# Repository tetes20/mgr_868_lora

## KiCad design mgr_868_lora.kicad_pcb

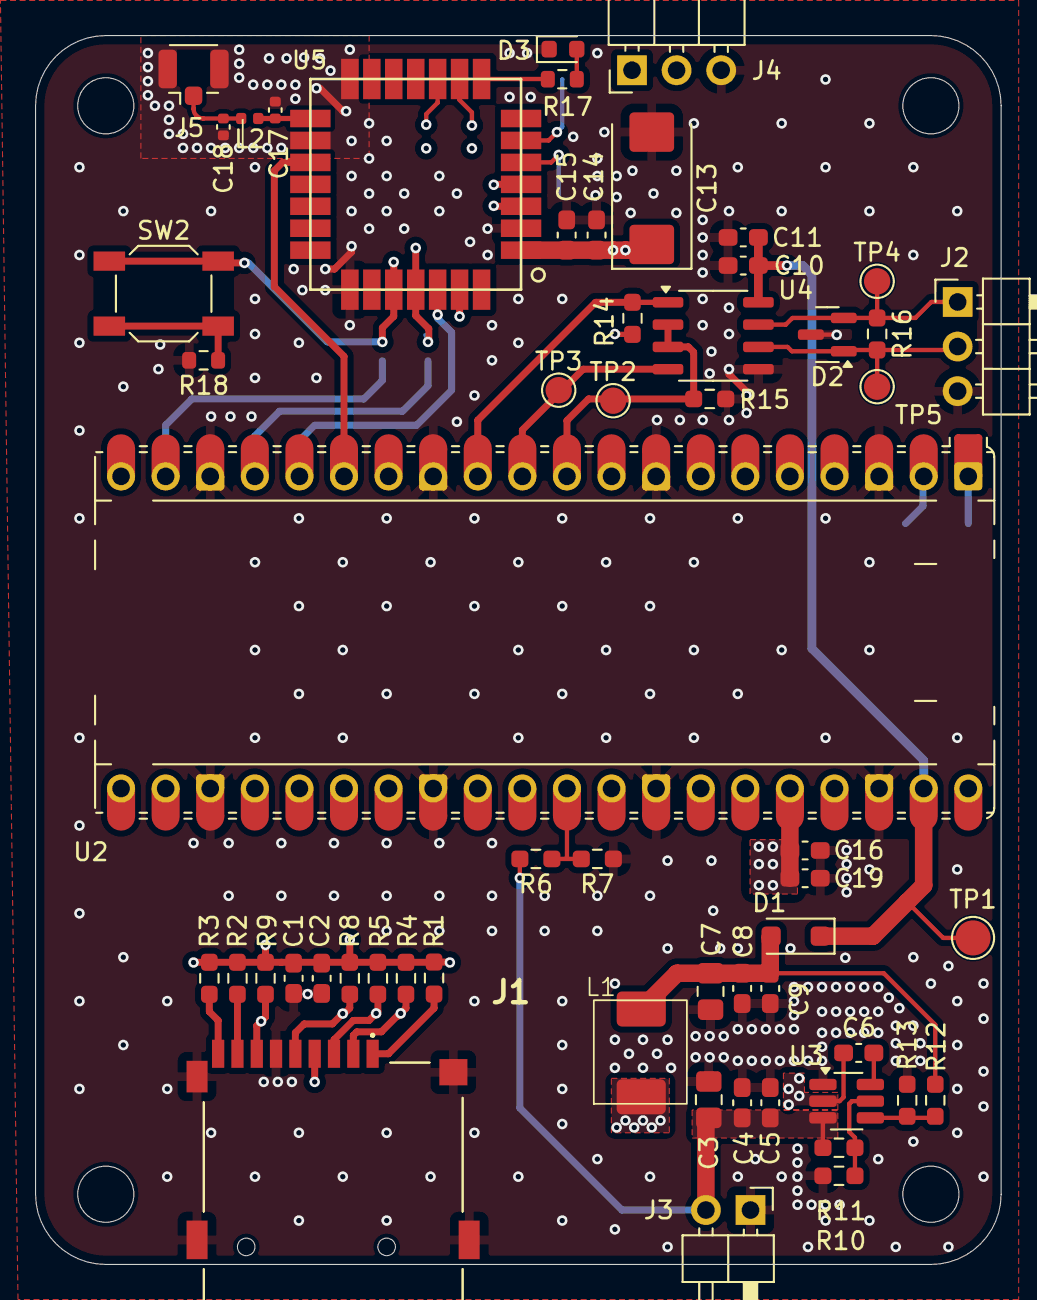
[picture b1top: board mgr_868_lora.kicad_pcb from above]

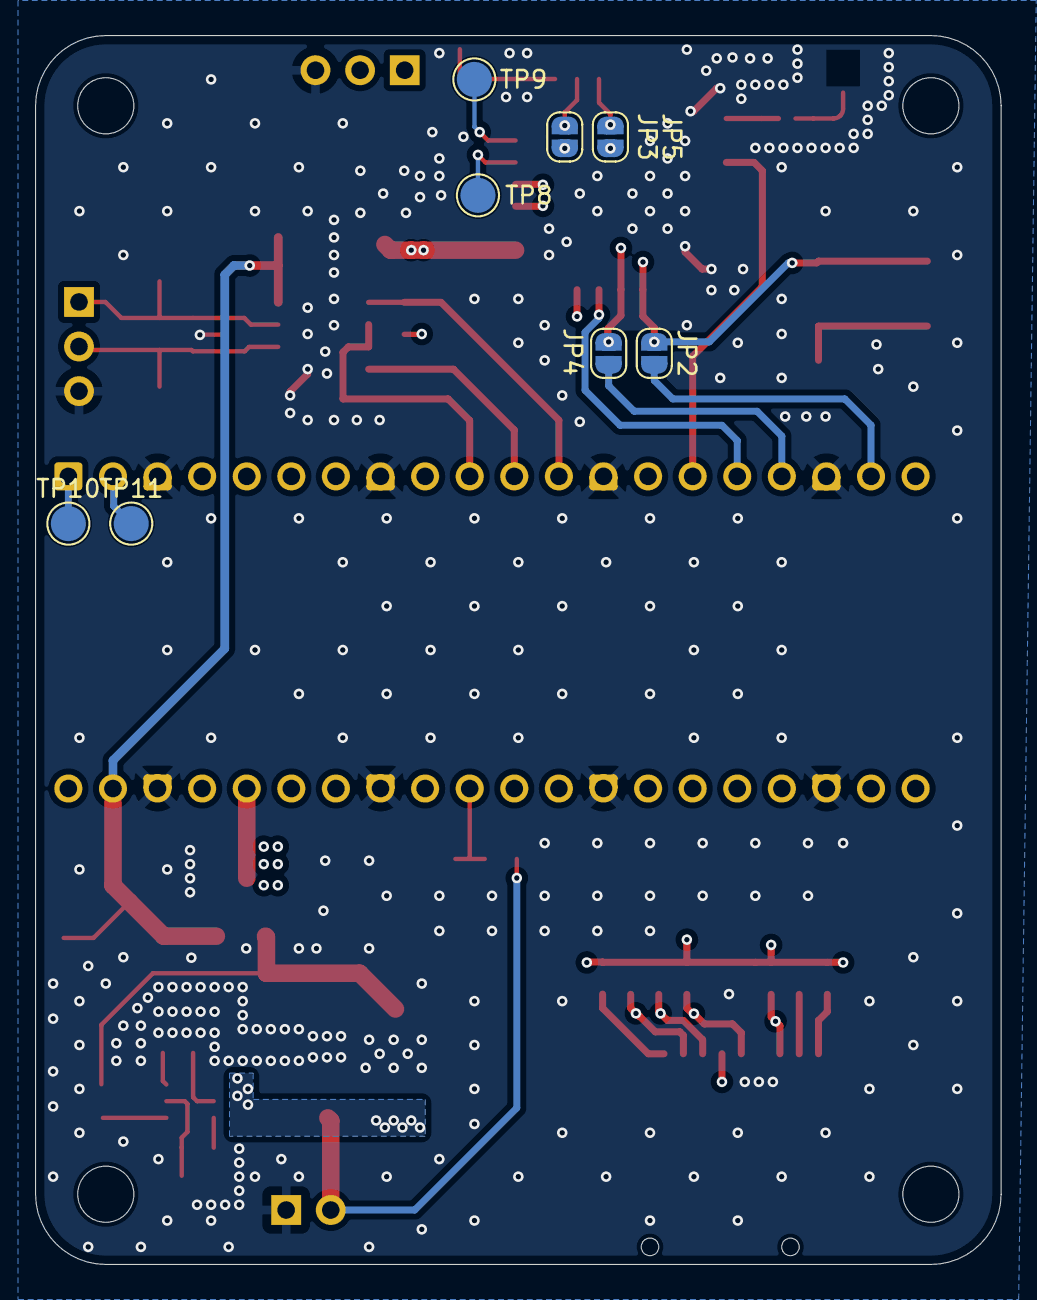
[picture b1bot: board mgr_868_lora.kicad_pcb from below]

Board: 4 copper layers, 55.0 x 70.0 mm, 68 parts (8 on the bottom side), 42 nets.

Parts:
C1: 4,7uF; C_0603_1608Metric_Pad1.08x0.95mm_HandSolder
C2, C5, C6, C9, C10, C15, C19: 100nF; C_0603_1608Metric_Pad1.08x0.95mm_HandSolder
C3, C7: 22uF; C_0805_2012Metric_Pad1.18x1.45mm_HandSolder
C4, C8, C11, C14, C16: 10uF; C_0603_1608Metric_Pad1.08x0.95mm_HandSolder
C13: 100uF; CP_EIA-7343-31_Kemet-D_Pad2.25x2.55mm_HandSolder
C17, C18: NMT; C_0402_1005Metric
D1: D_Schottky; D_SOD-123F
D2: SM36.TCT; SOT-23
D3: LED; LED_0603_1608Metric
H1, H2, H3, H4: MountingHole; MountingHole_3.2mm_M3
J1: Micro_SD_Card; MCSPQ08ASGTR
J2, J4: Conn_01x03; PinHeader_1x03_P2.54mm_Horizontal
J3: Conn_01x02; PinHeader_1x02_P2.54mm_Horizontal
J5: UFL; U.FL_Hirose_U.FL-R-SMT-1_Vertical
JP2, JP3, JP4, JP5: SolderJumper_2_Open; SolderJumper-2_P1.3mm_Open_RoundedPad1.0x1.5mm
L1: 3,3uH; HPI0-3R3
L2: NMT; L_0402_1005Metric
R1, R2, R3, R4, R5, R6, R7, R8, R9, R10, R11, R13, R14, R15: 10k; R_0603_1608Metric_Pad0.98x0.95mm_HandSolder
R12: 56k; R_0603_1608Metric_Pad0.98x0.95mm_HandSolder
R16: 120R; R_0603_1608Metric_Pad0.98x0.95mm_HandSolder
R17, R18: 1k; R_0603_1608Metric
SW2: SW_MEC_5E; SW_SPST_SKQG_WithStem
TP1, TP8, TP9, TP10, TP11: TestPoint; TestPoint_Pad_D2.0mm
TP2, TP3, TP4, TP5: TestPoint; TestPoint_Pad_D1.5mm
U2: RaspberryPi_Pico; RaspberryPi_Pico_Common_Unspecified
U3: TPS562201DDCR; SOT-23-6_Handsoldering
U4: SN75176BDR; SO-8_3.9x4.9mm_P1.27mm
U5: LoRa-E5

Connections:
+3V3: C1.1, C2.1, C13.1, C14.1, C15.1, C16.1, C19.1, J1.4 (VDD), R1.2, R2.2, R3.2, R4.2, R5.2, R8.2, R9.2, R14.1, U2.36 (3V3), U5.1 (VCC)
+5V: C10.1, C11.1, D1.1 (K), TP1.1, U2.39 (VSYS), U4.8 (VCC)
+BATT: C3.2, C4.2, C5.2, J3.2, R6.2, R10.2, U3.3 (VIN)
/CD: J1.9 (DET), R3.1
/DAT1: J1.8 (DAT1), R2.1
/DAT2: J1.1 (DAT2), R1.1
/RS485/RS485_A: D2.1 (K), J2.2, R16.2, TP5.1, U4.6 (A)
/RS485/RS485_B: D2.2 (K), J2.1, R16.1, TP4.1, U4.7 (B)
/RS485_RX: R14.2, U2.12 (GPIO9), U4.1 (R)
/RS485_R/T: R15.1, TP2.1, U2.10 (GPIO7), U4.2 (~RE), U4.3 (DE)
/RS485_TX: TP3.1, U2.11 (GPIO8), U4.4 (D)
/Radio/RADIO_CS: JP4.1 (A), U2.17 (GPIO13)
/Radio/RADIO_MISO: U2.16 (GPIO12), U5.26 (PB14)
/Radio/RADIO_MOSI: U2.20 (GPIO15), U5.27 (PA10)
/Radio/RADIO_RST: U2.15 (GPIO11), U5.17 (RST)
/Radio/RADIO_SCLK: JP2.1 (A), U2.19 (GPIO14)
/Radio/R_CS: JP4.2 (B), JP5.2 (B), U5.25 (PB9)
/Radio/R_SCLK: JP2.2 (B), JP3.2 (B), SW2.1, U5.24 (PB13~)
/Radio/SWCLK: J4.1, U5.4 (PA14)
/Radio/SWDIO: J4.2, U5.3 (PA13)
/Radio/UART_RX: JP5.1 (A), U5.10 (PB6)
/Radio/UART_TX: JP3.1 (A), U5.9 (PB7)
/SD_CS: J1.2 (DAT3/CD), R4.1, U2.22 (GPIO17)
/SD_MISO: J1.7 (DAT0), R9.1, U2.21 (GPIO16)
/SD_MOSI: J1.3 (CMD), R5.1, U2.25 (GPIO19)
/SD_SCLK: J1.5 (CLK), R8.1, U2.24 (GPIO18)
GND: C1.2, C2.2, C3.1, C4.1, C5.1, C7.1, C8.1, C9.1, C10.2, C11.2, C13.2, C14.2, C15.2, C16.2, C17.2, C18.2, C19.2, D2.3 (A), D3.1 (K), J1.6 (VSS), J1.MP1 (SHIELD), J1.MP2 (SHIELD), J1.MP3 (SHIELD), J1.MP4 (SHIELD), J2.3, J3.1, J4.3, J5.2 (Ext), R7.1, R11.1, R13.1, R15.2, R18.2, U2.3 (GND), U2.8 (GND), U2.13 (GND), U2.18 (GND), U2.23 (GND), U2.28 (GND), U2.33 (AGND), U2.38 (GND), U3.1 (GND), U4.5 (GND), U5.2 (GND), U5.14 (GND), U5.16 (GND), U5.22 (GND)
unnamed: C7.2, C8.2, C9.2, D1.2 (A), L1.2, R12.2
unnamed: D3.2 (A), R17.2
unnamed: C18.1, J5.1 (In), L2.2
unnamed: R18.1, SW2.2 (A)
unnamed: TP10.1, U2.1 (GPIO0)
unnamed: TP11.1, U2.2 (GPIO1)
unnamed: R6.1, R7.2, U2.31 (GPIO26_ADC0)
unnamed: R10.1, R11.2, U3.5 (EN)
unnamed: C6.2, L1.1, U3.2 (SW)
unnamed: C6.1, U3.6 (VBST)
unnamed: R12.1, R13.2, U3.4 (VFB)
unnamed: TP9.1, U5.6 (PA15)
unnamed: R17.1, U5.8 (PB3)
unnamed: TP8.1, U5.5 (PB15)
unnamed: C17.1, L2.1, U5.15 (RFIO)

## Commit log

2025-03-19 init commit
2025-03-19 to_review
